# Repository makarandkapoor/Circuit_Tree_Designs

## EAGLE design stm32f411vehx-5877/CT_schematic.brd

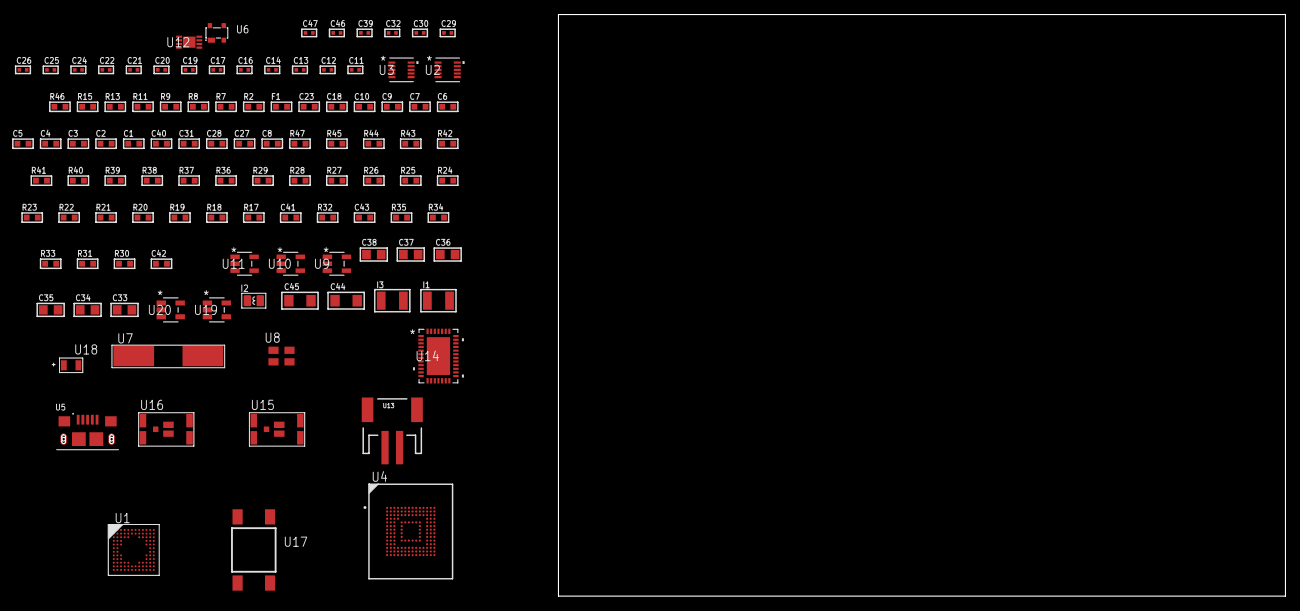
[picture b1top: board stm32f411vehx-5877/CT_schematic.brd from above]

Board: 2 copper layers, 168.3 x 80.0 mm, 108 parts (0 on the bottom side), 65 nets, no tracks yet.

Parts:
C1, C10, C18, C23: 1e-06; C0603
C2, C3, C4, C5, C6, C7: 1e-07; C0603
C8: 4.7e-06; C0603
C9: 1e-08; C0603
C11, C12, C16, C17, C19, C20, C21, C22, C24, C25, C26, C29, C30, C39: 1e-07; C0402
C13, C14: 1e-11; C0402
C27, C28, C31, C40: 2.2e-06; C0603
C32, C46, C47: 1e-08; C0402
C33, C34, C35, C36, C37, C38: 1e-05; C0805
C41: 2.45e-08; R0603
C42: 2.8258362168397e-09; R0603
C43: 7.105e-09; R0603
C44, C45: 1e-05; C1206
F1: 240.0; L0603
I1, I3: 1.5e-05; L1210
I2: 3.3e-06; L0806
R2: 1000.0; R0603
R7, R8: 4700.0; R0603
R9, R11, R13, R15: 2200.0; R0603
R17, R18, R19, R36, R38, R39, R42, R43, R44, R47: 10000.0; R0603
R20, R21, R22, R23, R24, R25, R26, R27, R28, R29: 34000.0; R0603
R30, R31, R33, R34, R35: 1000000.0; R0603
R32: 220000.0; R0603
R37: 75000.0; R0603
R40, R41: 95300.0; R0603
R45: 24000.0; R0603
R46: 2000.0; R0603
U1: STM32F411VEH6; UFBGA100
U2, U3: MAG3110FCR1; DFN-10
U4: mtfc4gmcdm; TFBGA-153
U5: 10118193-0001LF; FCI_10118193-0001LF
U6: prtr5v0u2ax; SOT143B
U7: ABLS-25.000MHZ-B2F-T
U8: ASEK-32.768KHz-ECST; ASEK
U9, U10, U11: ltc3406es5; TSOT-23-5
U12: MCP73831T-2ACI/MC; DFN8_2X3MC
U13: S2B-PH-SM4-TB(LF)(SN); JST-2-SMD
U14: LTC2928CUHF#PBF; QFN-38_UHF
U15, U16: IRF8306MTRPbF; IRF8306MTRPBF
U17: 4-1437565-2; SW_4-1437565-2
U18: Q65110A2395; LGM67K-G1J2-24-Z
U19, U20: nc7sz125m5x; NC7SZ125M5X

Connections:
CLK_CRYSTAL_U1_F1: C13.1, U1.F1, U7.1
CLK_CRYSTAL_U1_G1: C14.1, U1.G1, U7.2
CLK_U1_D1: U1.D1, U8.3
GND: C1.2, C2.2, C3.2, C4.2, C5.2, C6.2, C7.2, C8.2, C9.2, C10.2, C11.2, C12.2, C13.2, C14.2, C16.2, C17.2, C18.2, C19.2, C20.2, C21.2, C22.2, C23.2, C24.2, C25.2, C26.2, C27.2, C28.2, C29.2, C30.2, C31.2, C32.2, C33.2, C34.1, C34.2, C35.2, C36.1, C36.2, C37.2, C38.1, C38.2, C39.2, C40.2, C41.2, C42.2, C43.2, C44.2, C45.2, C46.2, C47.2, R2.2, R17.2, R30.2, R32.2, R34.2, R37.2, R40.2, R41.2, R42.2, R43.2, R44.2, R46.2, U1.D3, U1.F2, U1.F11, U1.F12, U1.J1, U1.K1, U2.5, U2.10, U3.5, U3.10, U4.C4, U4.E7, U4.G5, U4.H10, U4.K8, U4.N2, U4.N5, U4.P4, U4.P6, U5.5, U5.6, U5.7, U5.8, U5.9, U6.1, U8.2, U9.2, U10.2, U11.2, U12.6, U12.9, U13.2, U14.8, U14.9, U14.10, U14.12, U14.13, U14.24, U14.25, U14.30, U14.32, U14.39, U18.C, U19.1, U19.3, U20.1, U20.3
INPUT_USBPOWER_5V: C44.1, R47.2, U5.1, U6.4, U12.1, U12.2
NET_U1_A4: R17.1, U1.A4
NET_U1_A8: R15.1, U1.A8, U2.6
NET_U1_B4: R11.1, U1.B4, U3.6
NET_U1_B5: R9.1, U1.B5, U3.7
NET_U1_C11: C12.1, U1.C11
NET_U1_E3: R19.1, U1.E3
NET_U1_H2: R8.1, U1.H2, U20.4
NET_U1_H3: R18.1, U1.H3
NET_U1_L10: R13.1, U1.L10, U2.7
NET_U1_M1: C9.1, C10.1, F1.1, U1.L1, U1.M1
NET_U1_M12: U17.3, U17.4
NET_U2_1: C16.1, U2.1
NET_U2_4: C19.1, U2.4
NET_U3_1: C21.1, U3.1
NET_U3_4: C24.1, U3.4
NET_U4_C2: C28.1, C29.1, U4.C2
NET_U4_K5: R7.1, U4.K5, U19.4
NET_U9_3: I1.1, U9.3
NET_U9_5: R30.1, R31.1, U9.5
NET_U9_ATNET_3: I1.2, R31.2
NET_U10_3: I2.1, U10.3
NET_U10_5: R32.1, R33.1, U10.5
NET_U10_ATNET_3: I2.2, R33.2
NET_U11_3: I3.1, U11.3
NET_U11_5: R34.1, R35.1, U11.5
NET_U11_ATNET_3: I3.2, R35.2
NET_U12_5: R47.1, U12.5
NET_U12_8: R46.1, U12.8
NET_U14_3: R43.1, U14.3
NET_U14_6: R40.1, U14.6
NET_U14_7: R41.1, U14.7
NET_U14_16: R42.1, R45.1, U14.16
NET_U14_18: R39.1, U14.18
NET_U14_19: R38.1, U14.19, U14.20
NET_U14_21: R36.1, R37.1, U14.21, U19.2, U20.2
NET_U14_26: C42.1, U14.26
NET_U14_27: C41.1, U14.27
NET_U14_28: C43.1, U14.28
NET_U14_38: R44.1, U14.38
NET_U15_3: U14.2, U15.3
NET_U16_3: U14.37, U16.3
NET_U17_1: R2.1, U17.1, U17.2
PROC_SDIO_CK: R29.1, U1.B10, U4.M6
PROC_SDIO_CMD: R28.1, U1.C8, U4.M5
PROC_SDIO_D0: R20.1, U1.A7, U4.A3
PROC_SDIO_D1: R21.1, U1.D11, U4.A4
PROC_SDIO_D2: R22.1, U1.B11, U4.A5
PROC_SDIO_D3: R23.1, U1.C5, U4.B2
PROC_SDIO_D4: R24.1, U1.A3, U4.B3
PROC_SDIO_D5: R25.1, U1.B3, U4.B4
PROC_SDIO_D6: R26.1, U1.E12, U4.B5
PROC_SDIO_D7: R27.1, U1.E11, U4.B6
PROC_USB_OTG_FS_DM: U5.2, U6.3
PROC_USB_OTG_FS_DP: U5.3, U6.2
VCC_3V7: C39.1, C40.1, C45.1, R36.2, R38.2, R39.2, R45.2, U12.3, U12.4, U13.1, U14.11, U14.22, U15.1, U15.2, U15.6, U15.7, U16.1, U16.2, U16.6, U16.7
VCC_S1_3V7: C33.1, C35.1, U9.4, U10.4, U15.4, U15.5
VCC_S2_3V7: C37.1, U11.4, U16.4, U16.5
VCC_TIER1_1V2: C11.1, C34.2, I1.2, R31.2, U1.L11
VCC_TIER1_3V3: C1.1, C2.1, C3.1, C4.1, C5.1, C6.1, C7.1, C8.1, C17.1, C18.1, C20.1, C22.1, C23.1, C25.1, C26.1, C27.1, C30.1, C31.1, C32.1, C36.2, C46.1, C47.1, F1.2, I2.2, R7.2, R8.2, R9.2, R11.2, R13.2, R15.2, R18.2, R19.2, R20.2, R21.2, R22.2, R23.2, R24.2, R25.2, R26.2, R27.2, R28.2, R29.2, R33.2, U1.C4, U1.E2, U1.G2, U1.G11, U1.G12, U2.2, U2.8, U3.2, U3.8, U4.C6, U4.E6, U4.F5, U4.J10, U4.K9, U4.M4, U4.N4, U4.P3, U4.P5, U8.4, U19.5, U20.5
VCC_TIER2_1V2: C38.2, I3.2, R35.2

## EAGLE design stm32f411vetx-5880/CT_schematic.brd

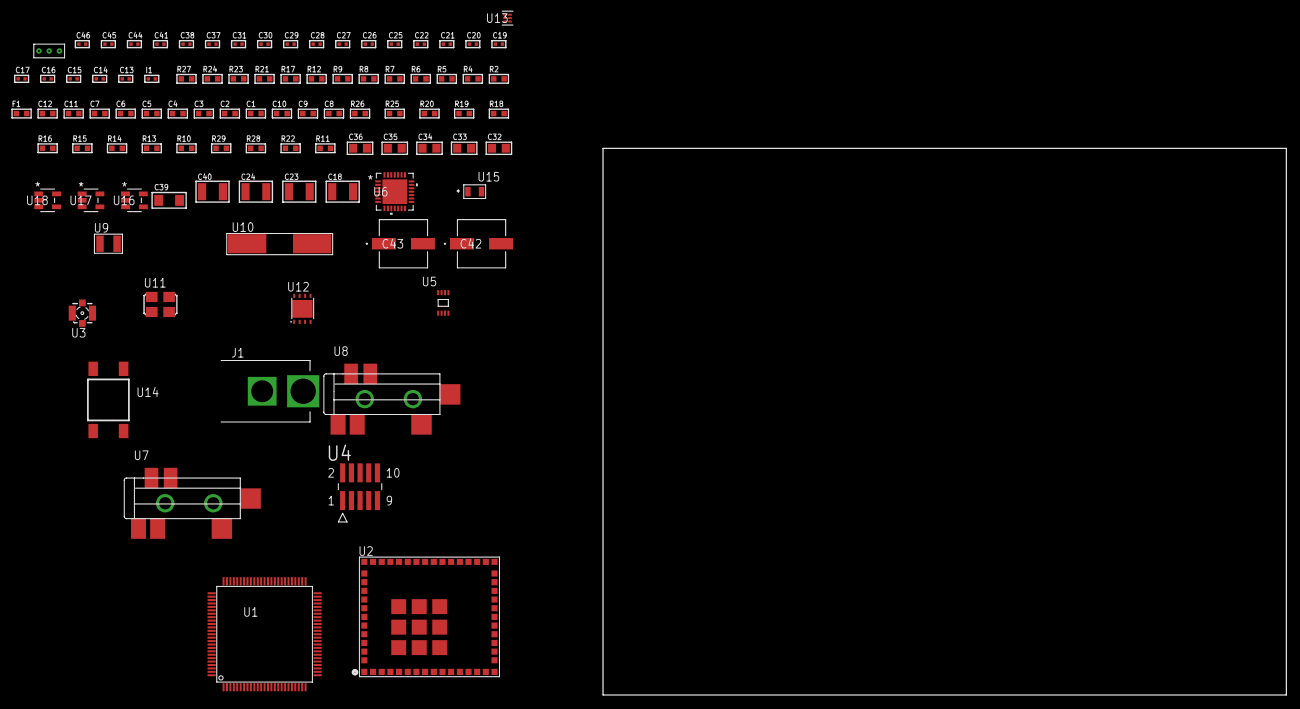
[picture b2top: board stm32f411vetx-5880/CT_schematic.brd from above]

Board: 2 copper layers, 100.0 x 80.0 mm, 95 parts (0 on the bottom side), 44 nets, no tracks yet.

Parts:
C1, C12: 1e-06; C0603
C2, C3, C4, C5, C6, C7: 1e-07; C0603
C8: 4.7e-06; C0603
C9, C10: 2.2e-06; C0603
C11: 1e-08; C0603
C13, C14, C15, C16: 1e-11; C0402
C17: 1e-12; C0402
C18, C23, C24: 2.2e-05; C1210
C19, C20, C21, C27, C28, C29, C30, C31, C41: 1e-07; C0402
C22, C37, C38, C44, C45, C46: 1e-08; C0402
C25, C26: 1e-09; C0402
C32, C33, C34, C35, C36: 1e-05; C0805
C39: 1e-05; C1206
C40: 1e-05; C1210
C42, C43: 0.0001; EXV-9H
F1: 240.0; L0603
I1: 3.6e-09; C0402
J1: PJ-037B; PJ-037B_PACKAGE
R2, R24: 1000.0; R0603
R4, R5: 4700.0; R0603
R6, R7, R8, R9: 2200.0; R0603
R10, R13, R14, R15, R16, R25, R26: 10000.0; R0603
R11, R22: 100000.0; R0603
R12: 2700.0; R0603
R17: 5.0; R0603
R18, R19, R20: 47000.0; R0603
R21: 680.0; R0603
R23: 2231.0; R0603
R27: 9100.0; R0603
R28: 680000.0; R0603
R29: 120000.0; R0603
U1: STM32F411VET6; LQFP100
U2: CC3200MODR1M2AMOBT; LGA63S127P16X13_2050X1750X150
U3: 73412-0114; COAXIAL_C
U4: FTSH-105-01-L-DV-K; SAMTEC_FTSH-105-01-L-DV-K
U5: 24AA01T-I/MNY; TDFN-8/6MM
U6: WM8731CLSEFL; QFN-28
U7, U8: SJ-43515TS-SMT-TR
U9: ABS07-32.768KHZ-7-T
U10: ABLS-25.000MHZ-B2F-T
U11: ASFL1-12.288MHZ-EC-T; ASFL1
U12: LP3878SDX-ADJ/NOPB; WSON-8
U13: TPS3895ADRYR; SON-6
U14: 4-1437565-2; SW_4-1437565-2
U15: Q65110A2395; LGM67K-G1J2-24-Z
U16, U17, U18: nc7sz125m5x; NC7SZ125M5X
U19: Dummy; DUMMY_PACKAGE_205

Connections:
CLK_CRYSTAL_U1_8: C13.1, U1.8, U9.1
CLK_CRYSTAL_U1_9: C14.1, U1.9, U9.2
CLK_CRYSTAL_U1_12: C15.1, U1.12, U10.1
CLK_CRYSTAL_U1_13: C16.1, U1.13, U10.2
CLK_U6_1: U6.1, U11.3
GND: C1.2, C2.2, C3.2, C4.2, C5.2, C6.2, C7.2, C8.2, C9.2, C10.2, C11.2, C12.2, C13.2, C14.2, C15.2, C16.2, C17.2, C18.2, C19.2, C20.2, C21.2, C22.2, C26.2, C27.2, C28.2, C29.2, C30.2, C31.2, C32.2, C33.2, C34.2, C35.2, C36.2, C37.2, C38.2, C39.2, C40.2, C41.2, C42.2, C43.2, C44.2, C45.2, C46.2, J1.2, R2.2, R10.2, R11.2, R12.2, R16.2, R17.2, R18.2, R19.2, R20.2, R24.2, R27.2, R29.2, U1.10, U1.20, U1.27, U1.49, U1.74, U1.99, U2.1, U2.2, U2.16, U2.27, U2.28, U2.30, U2.32, U2.38, U2.43, U2.55, U2.56, U2.57, U2.58, U2.59, U2.60, U2.61, U2.62, U2.63, U3.1, U3.2, U3.3, U3.4, U4.3, U4.5, U5.4, U5.7, U6.4, U6.15, U6.19, U6.25, U6.26, U6.29, U7.1, U8.1, U11.2, U12.3, U12.PAD, U13.2, U15.C, U16.2, U16.3, U17.1, U17.3, U18.1, U18.3, U19.1
NET_U1_14: R5.1, U1.14, U18.4
NET_U1_22: C11.1, C12.1, F1.1, U1.21, U1.22
NET_U1_47: R8.1, U1.47, U5.6
NET_U1_48: C9.1, U1.48
NET_U1_73: C10.1, U1.73
NET_U1_92: R6.1, U1.92, U2.3
NET_U1_93: R7.1, U1.93, U2.4
NET_U1_94: R10.1, U1.94
NET_U1_96: R9.1, U1.96, U5.5
NET_U1_98: U14.3, U14.4
NET_U2_21: R11.1, U2.21
NET_U2_23: R12.1, U2.23
NET_U2_35: R4.1, U2.35, U17.4
NET_U3_1: C17.1, I1.1, U3.1
NET_U4_9: R17.1, U4.9
NET_U6_20: C31.1, C36.1, U6.20
NET_U7_2: C24.1, R19.1, U7.2
NET_U7_5: C23.1, R18.1, U7.5
NET_U8_5: C25.1, C26.1, R20.1, R21.1, U8.5
NET_U12_1: C38.1, U12.1
NET_U12_6: R23.2, R24.1, U12.6
NET_U12_8: R22.1, U12.8
NET_U13_1: R26.1, R27.1, U13.1
NET_U13_3: R28.2, R29.1, U13.3
NET_U13_4: R25.1, U13.4, U16.4, U17.2, U18.2
NET_U14_1: R2.1, U14.1, U14.2
PROC_ADC1_IN1: U1.24, U19.3
PROC_ADC1_IN2: U1.25, U19.2
PROC_I2S1_CK: U1.30, U6.7
PROC_I2S1_SD: U1.32, U6.8
PROC_I2S1_WS: U1.29, U6.9, U6.11
PROC_SYS_JTCK_SWCLK: R16.1, U1.76, U4.4
PROC_SYS_JTDI: R14.1, U1.77, U4.8
PROC_SYS_JTDO_SWO: U1.89, U4.6
PROC_SYS_JTMS_SWDIO: R15.1, U1.72, U4.2
RST_OUT_U4_JTAG_RST_B: R13.1, U4.10, U16.1
VCC_S1_5V4: C39.1, C42.1, C43.1, J1.1, R22.2, U12.4
VCC_TIER1_3V3: C1.1, C2.1, C3.1, C4.1, C5.1, C6.1, C7.1, C8.1, C18.1, C19.1, C20.1, C21.1, C22.1, C27.1, C28.1, C29.1, C30.1, C32.1, C33.1, C34.1, C35.1, C37.1, C40.1, C41.1, C44.1, C45.1, C46.1, F1.2, R4.2, R5.2, R6.2, R7.2, R8.2, R9.2, R13.2, R14.2, R15.2, R23.1, R25.2, R26.2, R28.1, U1.6, U1.11, U1.19, U1.28, U1.50, U1.75, U1.100, U2.36, U2.37, U2.40, U4.1, U5.8, U6.3, U6.5, U6.12, U6.18, U11.4, U12.5, U13.6, U16.5, U17.5, U18.5

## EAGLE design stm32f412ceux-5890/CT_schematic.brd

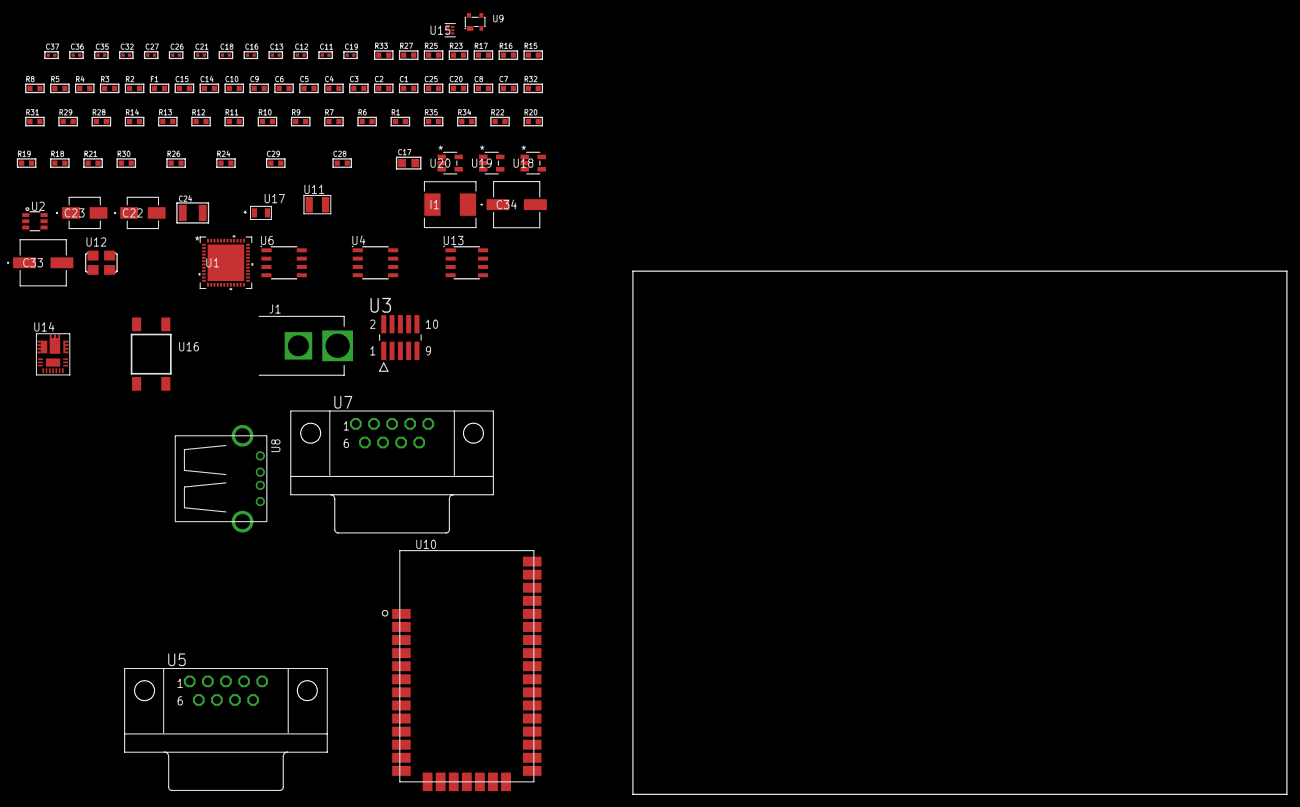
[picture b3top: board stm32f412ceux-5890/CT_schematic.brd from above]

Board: 2 copper layers, 100.0 x 80.0 mm, 93 parts (0 on the bottom side), 59 nets, no tracks yet.

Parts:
C1, C10, C14, C15: 1e-06; C0603
C2, C3, C4, C5, C6: 1e-07; C0603
C7: 4.7e-06; C0603
C8, C25: 2.2e-06; C0603
C9: 1e-08; C0603
C11, C12: 1e-11; C0402
C13, C16, C18, C26, C27, C32: 1e-07; C0402
C17: 1e-05; C0805
C19: 4.7e-11; C0402
C20: 8.2e-12; C0603
C21, C35, C36, C37: 1e-08; C0402
C22: 1e-06; EXV-9B
C23: 2.2e-06; EXV-9B
C24: 0.0001; C1210
C28: 8.6971073877236e-09; R0603
C29: 2.9649229730876e-07; R0603
C33, C34: 0.0001; EXV-9H
F1: 240.0; L0603
I1: 6.8e-07; IND25X25CZ
J1: PJ-037B; PJ-037B_PACKAGE
R1, R7, R9, R10, R11, R12, R13, R14, R31, R32: 10000.0; R0603
R2: 1000.0; R0603
R3: 1600.5; R0603
R4, R5: 4700.0; R0603
R6: 47000.0; R0603
R8: 1270.0; R0603
R15: 5.0; R0603
R16, R17: 120.0; R0603
R18: 470000.0; R0603
R19, R20, R22: 100000.0; R0603
R21: 164658.62; R0603
R23: 0.1; R0603
R24: 4030.2416170974; R0603
R25: 453.0; R0603
R26: 58.613333333333; R0603
R27: 130.0; R0603
R28: 39000.0; R0603
R29: 49900.0; R0603
R30: 5147.5789473684; R0603
R33: 9100.0; R0603
R34: 680000.0; R0603
R35: 120000.0; R0603
U1: STM32F412CEU6; UFQFPN48
U2: MAX4995AAUT+T; SOT-23-6
U3: FTSH-105-01-L-DV-K; SAMTEC_FTSH-105-01-L-DV-K
U4: MCP2562-E/SN; SOIC-8
U5, U7: 182-009-113R531; 182-009-MALE
U6: SN65HVD230D; SOIC-8
U8: 61400416021; USB-A-H
U9: prtr5v0u2ax; SOT143B
U10: XB24CZ7UIS-004
U11: ABS07-32.768KHZ-7-T
U12: ASFL1-25MHZ-NCS; ASFL1
U13: LP2954AIMX/NOPB; LP2954
U14: IR3899MTR1PBF
U15: TPS3895ADRYR; SON-6
U16: 4-1437565-2; SW_4-1437565-2
U17: Q65110A2395; LGM67K-G1J2-24-Z
U18, U19, U20: nc7sz125m5x; NC7SZ125M5X

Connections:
CLK_CRYSTAL_U1_3: C11.1, U1.3, U11.1
CLK_CRYSTAL_U1_4: C12.1, U1.4, U11.2
CLK_U1_5: U1.5, U12.3
GND: C1.2, C2.2, C3.2, C4.2, C5.2, C6.2, C7.2, C8.2, C9.2, C10.2, C11.2, C12.2, C13.2, C14.2, C15.2, C16.2, C17.2, C18.2, C19.2, C20.2, C21.2, C22.2, C23.2, C25.2, C26.2, C27.2, C32.2, C33.2, C34.2, C35.2, C36.2, C37.2, J1.2, R2.2, R6.2, R7.2, R8.2, R10.2, R14.2, R15.2, R18.2, R22.2, R23.1, R23.2, R25.2, R28.2, R30.2, R33.2, R35.2, U1.8, U1.23, U1.35, U1.47, U1.49, U2.2, U3.3, U3.5, U4.2, U4.8, U5.5, U6.2, U7.5, U8.4, U8.5, U8.6, U9.1, U10.1, U10.11, U10.13, U10.22, U10.35, U12.2, U13.4, U14.4, U14.11, U14.17, U15.2, U17.C, U18.2, U18.3, U19.1, U19.3, U20.1, U20.3
NET_U1_7: R5.1, U1.7, U20.4
NET_U1_9: C9.1, C10.1, F1.1, U1.9
NET_U1_22: C8.1, U1.22
NET_U1_31: R8.1, U1.31
NET_U1_42: R3.1, U1.42, U17.A
NET_U1_43: R1.1, U1.43, U16.3, U16.4
NET_U1_44: R7.1, U1.44
NET_U2_3: R6.1, U2.3
NET_U3_9: R15.1, U3.9
NET_U4_6: R16.2, U4.6
NET_U5_2: R16.2, U4.6, U5.2
NET_U5_3: R16.1, U4.7, U5.3
NET_U6_6: R17.2, U6.6
NET_U6_8: R18.1, U6.8
NET_U7_2: R17.2, U6.6, U7.2
NET_U7_3: R17.1, U6.7, U7.3
NET_U10_6: R4.1, U10.6, U19.4
NET_U13_3: R20.1, U13.3
NET_U13_5: R19.1, U13.5
NET_U13_7: R21.2, R22.1, U13.7
NET_U14_1: C28.1, R24.1, R25.1, R26.1, R27.1, U14.1, U14.8
NET_U14_2: C27.1, U14.2
NET_U14_3: C28.2, C29.1, C29.2, U14.3
NET_U14_5: R28.1, U14.5
NET_U14_10: C25.1, U14.10
NET_U14_12: C24.1, I1.1, U14.12
NET_U14_14: C24.2, U14.14
NET_U14_15: R29.1, R30.1, U14.15
NET_U14_ATNET_3: I1.2, R24.2
NET_U14_ATNET_4: C29.2, R26.2
NET_U15_1: R32.1, R33.1, U15.1
NET_U15_3: R34.2, R35.1, U15.3
NET_U15_4: R31.1, U15.4, U18.4, U19.2, U20.2
NET_U16_1: R2.1, U16.1, U16.2
PROC_CAN1_RX: U1.45, U6.4
PROC_CAN1_TX: U1.46, U6.1
PROC_CAN2_RX: U1.25, U4.4
PROC_CAN2_TX: U1.26, U4.1
PROC_GPIO_TO_U1_USB_FAULT: R9.1, U1.6, U2.6
PROC_GPIO_TO_U1_VBUS_EN: R10.1, U1.2, U2.4
PROC_SPI1_MISO: U1.16, U10.17
PROC_SPI1_MOSI: U1.17, U10.16
PROC_SPI1_NSS: U1.14, U10.15
PROC_SPI1_SCK: U1.15, U10.14
PROC_SYS_JTCK_SWCLK: R14.1, U1.37, U3.4
PROC_SYS_JTDI: R12.1, U1.38, U3.8
PROC_SYS_JTDO_SWO: U1.39, U3.6
PROC_SYS_JTMS_SWDIO: R13.1, U1.34, U3.2
PROC_USB_OTG_FS_DM: U1.32, U8.2, U9.3
PROC_USB_OTG_FS_DP: U1.33, U8.3, U9.2
PROC_USB_OTG_FS_VBUS: U1.30, U2.1, U8.1, U9.4
RST_OUT_U3_JTAG_RST_B: R11.1, U3.10, U18.1
VCC_S1_16V8: C22.1, C26.1, C33.1, C34.1, J1.1, R20.2, R29.2, U13.8, U14.9
VCC_TIER1_3V3: C1.1, C2.1, C3.1, C4.1, C5.1, C6.1, C7.1, C13.1, C15.1, C16.1, C17.1, C18.1, C19.1, C20.1, C21.1, C23.1, C32.1, C35.1, C36.1, C37.1, F1.2, R1.2, R3.2, R4.2, R5.2, R9.2, R11.2, R12.2, R13.2, R19.2, R21.1, R31.2, R32.2, R34.1, U1.1, U1.24, U1.36, U1.48, U3.1, U4.5, U6.3, U10.2, U10.27, U12.4, U13.1, U15.6, U18.5, U19.5, U20.5
VCC_TIER1_5V0: C14.1, I1.2, R24.2, U2.5, U4.3

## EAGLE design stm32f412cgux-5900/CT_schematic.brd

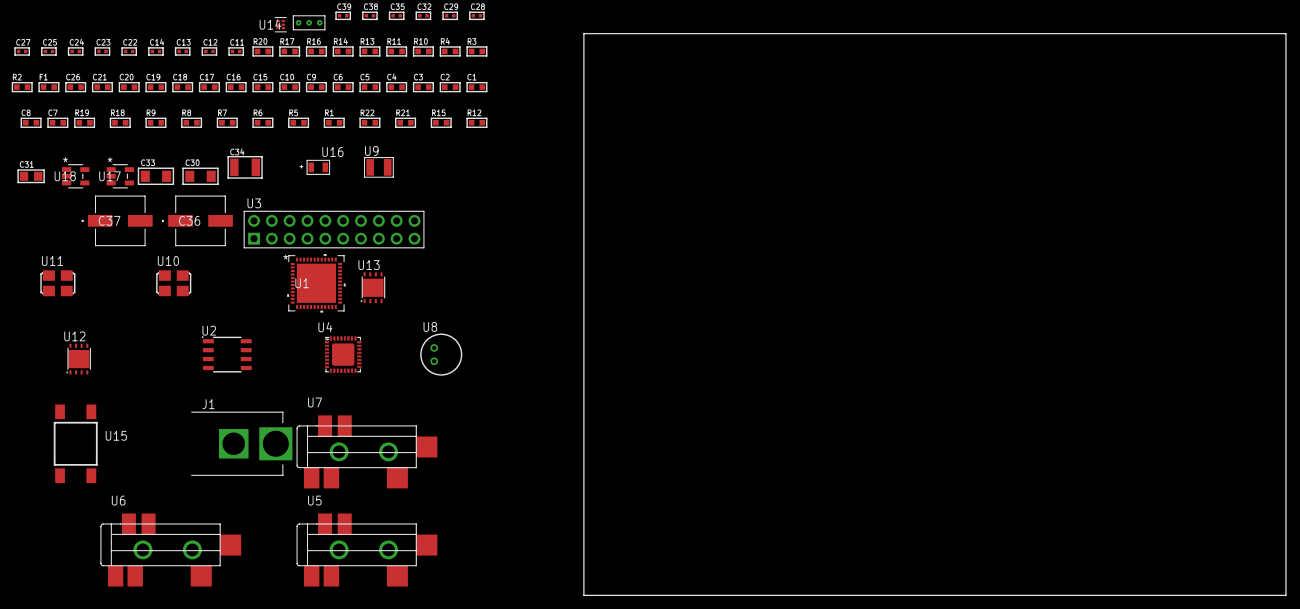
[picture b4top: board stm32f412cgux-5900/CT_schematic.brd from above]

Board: 2 copper layers, 100.0 x 80.0 mm, 82 parts (0 on the bottom side), 52 nets, no tracks yet.

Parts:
C1, C10, C15, C16, C17, C18, C19, C20, C21, C26: 1e-06; C0603
C2, C3, C4, C5, C6: 1e-07; C0603
C7: 4.7e-06; C0603
C8: 2.2e-06; C0603
C9: 1e-08; C0603
C11, C12: 1e-11; C0402
C13, C27, C28, C29, C32, C38, C39: 1e-08; C0402
C14, C22, C23, C24, C25, C35: 1e-07; C0402
C30, C33: 1e-05; C1206
C31: 1e-05; C0805
C34: 1e-05; C1210
C36, C37: 0.0001; EXV-9H
F1: 240.0; L0603
J1: PJ-037B; PJ-037B_PACKAGE
R1, R5, R6, R7, R8, R9, R18, R19: 10000.0; R0603
R2, R14, R17: 1000.0; R0603
R3: 1600.5; R0603
R4: 4700.0; R0603
R10, R11: 1270.0; R0603
R12, R15: 100000.0; R0603
R13: 200.0; R0603
R16: 2231.0; R0603
R20: 9100.0; R0603
R21: 680000.0; R0603
R22: 120000.0; R0603
U1: STM32F412CGU6; UFQFPN48
U2: AT25640B-SSHL-T; SOIC-8
U3: TST-110-05-T-D-RA
U4: SGTL5000XNAA3; QFN-32
U5, U6, U7: SJ-43515TS-SMT-TR
U8: WM-64PCT; WM-64PC
U9: ABS07-32.768KHZ-7-T
U10: ASFL-24.57MHZ-NCS; ASFL1
U11: ASFL1-25MHZ-NCS; ASFL1
U12, U13: LP3878SDX-ADJ/NOPB; WSON-8
U14: TPS3895ADRYR; SON-6
U15: 4-1437565-2; SW_4-1437565-2
U16: Q65110A2395; LGM67K-G1J2-24-Z
U17, U18: nc7sz125m5x; NC7SZ125M5X
U19: Dummy; DUMMY_PACKAGE_166

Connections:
CLK_CRYSTAL_U1_3: C11.1, U1.3, U9.1
CLK_CRYSTAL_U1_4: C12.1, U1.4, U9.2
CLK_U1_5: U1.5, U11.3
CLK_U4_21: U4.21, U10.3
GND: C1.2, C2.2, C3.2, C4.2, C5.2, C6.2, C7.2, C8.2, C9.2, C10.2, C11.2, C12.2, C13.2, C14.2, C22.2, C23.2, C24.2, C25.2, C26.2, C27.2, C28.2, C29.2, C30.2, C31.2, C32.2, C33.2, C34.2, C35.2, C36.2, C37.2, C38.2, C39.2, J1.2, R2.2, R5.2, R11.2, R14.2, R17.2, R20.2, R22.2, U1.8, U1.23, U1.35, U1.47, U1.49, U2.4, U3.4, U3.6, U3.8, U3.10, U3.12, U3.14, U3.16, U3.18, U3.20, U4.1, U4.3, U4.7, U4.EXP, U6.1, U7.1, U8.2, U10.2, U11.2, U12.3, U12.PAD, U13.3, U13.PAD, U14.2, U16.C, U17.2, U17.3, U18.1, U18.3, U19.1
NET_U1_7: R4.1, U1.7, U18.4
NET_U1_9: C9.1, C10.1, F1.1, U1.9
NET_U1_22: C8.1, U1.22
NET_U1_44: R5.1, U1.44
NET_U1_45: R3.1, U1.45, U16.A
NET_U1_46: R1.1, U1.46, U15.3, U15.4
NET_U2_3: R6.1, U2.3
NET_U2_7: R8.1, U2.7
NET_U4_10: C25.1, U4.10
NET_U4_29: R10.1, U4.29
NET_U4_31: R11.1, U4.31
NET_U5_1: U4.4, U5.1
NET_U5_2: U4.2, U5.2
NET_U5_5: U4.6, U5.5
NET_U6_2: C16.1, U6.2
NET_U6_5: C15.1, U6.5
NET_U7_2: C18.1, C19.1, U7.2
NET_U7_5: C17.1, U7.5
NET_U7_13: C18.2, C19.2
NET_U8_1: C20.1, C21.1, C26.1, U4.16, U8.1
NET_U8_15: C20.2, C21.2
NET_U12_1: C29.1, U12.1
NET_U12_6: R13.2, R14.1, U12.6
NET_U12_8: R12.1, U12.8
NET_U13_1: C32.1, U13.1
NET_U13_6: R16.2, R17.1, U13.6
NET_U13_8: R15.1, U13.8
NET_U14_1: R19.1, R20.1, U14.1
NET_U14_3: R21.2, R22.1, U14.3
NET_U14_4: R18.1, U14.4, U17.4, U18.2
NET_U15_1: R2.1, U15.1, U15.2
PROC_I2S1_CK: U1.15, U4.24
PROC_I2S1_SD: U1.17, U4.26
PROC_I2S1_WS: U1.14, U4.23
PROC_SPI2_MISO: U1.27, U2.2
PROC_SPI2_MOSI: U1.28, U2.5
PROC_SPI2_NSS: R7.1, U1.25, U2.1
PROC_SPI2_SCK: U1.21, U2.6
PROC_SYS_JTCK_SWCLK: U1.37, U3.9
PROC_SYS_JTDO_SWO: U1.39, U3.13
PROC_SYS_JTMS_SWDIO: U1.34, U3.7
PROC_TIM1_CH2: U1.30, U19.2
PROC_TIM1_CH4: U1.32, U19.3
RST_OUT_U3_SRESET_B: R9.1, U3.15, U17.1
VCC_S1_9V6: C30.1, C33.1, C36.1, C37.1, J1.1, R12.2, R15.2, U12.4, U13.4
VCC_TIER1_1V2: C22.1, C31.1, R13.1, U4.30, U12.5
VCC_TIER1_3V3: C1.1, C2.1, C3.1, C4.1, C5.1, C6.1, C7.1, C13.1, C14.1, C23.1, C24.1, C27.1, C28.1, C34.1, C35.1, C38.1, C39.1, F1.2, R1.2, R3.2, R4.2, R6.2, R7.2, R8.2, R9.2, R10.2, R16.1, R18.2, R19.2, R21.1, U1.1, U1.24, U1.36, U1.48, U2.8, U3.1, U4.5, U4.20, U10.4, U11.4, U13.5, U14.6, U17.5, U18.5

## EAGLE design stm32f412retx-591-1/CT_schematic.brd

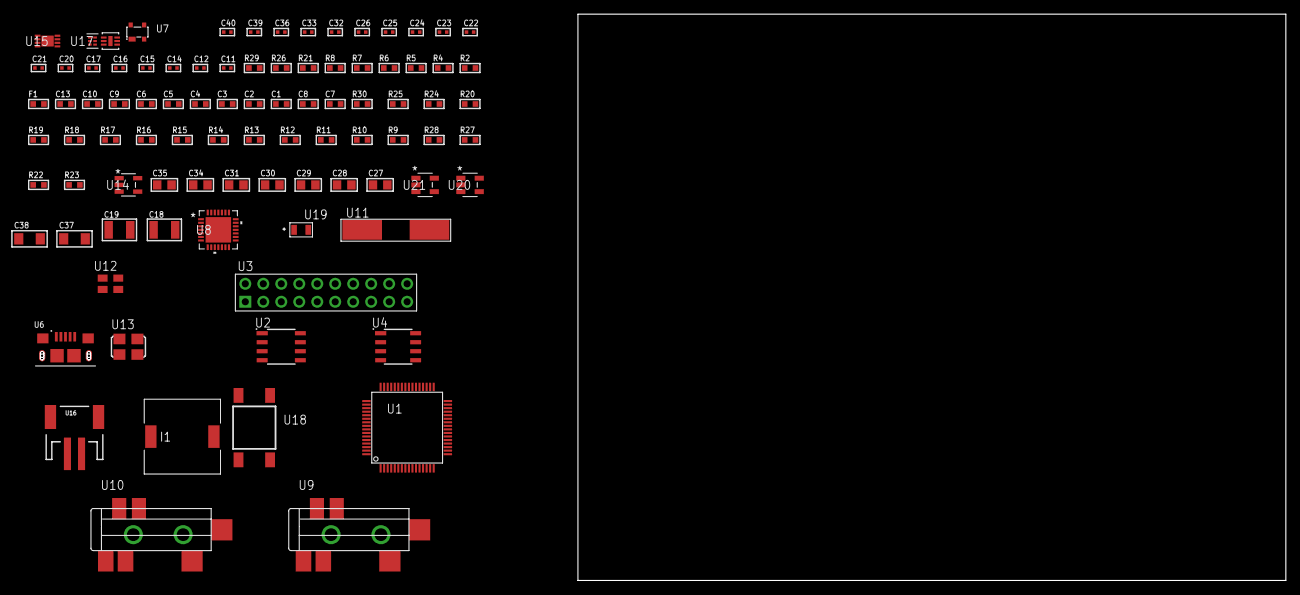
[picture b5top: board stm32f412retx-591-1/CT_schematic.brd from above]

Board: 2 copper layers, 175.9 x 80.0 mm, 91 parts (0 on the bottom side), 50 nets, no tracks yet.

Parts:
C1, C10, C13: 1e-06; C0603
C2, C3, C4, C5, C6: 1e-07; C0603
C7: 4.7e-06; C0603
C8: 2.2e-06; C0603
C9: 1e-08; C0603
C11, C12: 1e-11; C0402
C14, C16, C32, C33, C39, C40: 1e-08; C0402
C15, C17, C22, C23, C24, C25, C26, C36: 1e-07; C0402
C18, C19: 2.2e-05; C1210
C20, C21: 1e-09; C0402
C27, C28, C29, C30, C31, C34, C35: 1e-05; C0805
C37, C38: 1e-05; C1206
F1: 240.0; L0603
I1: 5.2e-06; DR1040
R2: 1000.0; R0603
R4: 4700.0; R0603
R5, R6, R7, R8: 2200.0; R0603
R9, R10, R11, R12, R13, R14, R15, R16, R17, R24, R25, R30: 10000.0; R0603
R18, R19, R20: 47000.0; R0603
R21: 680.0; R0603
R22: 220000.0; R0603
R23: 1000000.0; R0603
R26: 9100.0; R0603
R27: 680000.0; R0603
R28: 120000.0; R0603
R29: 2000.0; R0603
U1: STM32F412RET6; LQFP64
U2: AT25M01-SSHM-T; SOIC-8
U3: TST-110-05-T-D-RA
U4: AT24C02D-SSHM-T; AT24C02D
U5: SI7006-A20-IM; DFN-6
U6: 10118193-0001LF; FCI_10118193-0001LF
U7: prtr5v0u2ax; SOT143B
U8: WM8731CLSEFL; QFN-28
U9, U10: SJ-43515TS-SMT-TR
U11: ABLS-25.000MHZ-B2F-T
U12: ASEK-32.768KHz-ECST; ASEK
U13: ASFL1-12.288MHZ-EC-T; ASFL1
U14: ltc3406es5; TSOT-23-5
U15: MCP73831T-2ACI/MC; DFN8_2X3MC
U16: S2B-PH-SM4-TB(LF)(SN); JST-2-SMD
U17: TPS3895ADRYR; SON-6
U18: 4-1437565-2; SW_4-1437565-2
U19: Q65110A2395; LGM67K-G1J2-24-Z
U20, U21: nc7sz125m5x; NC7SZ125M5X

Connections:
CLK_CRYSTAL_U1_5: C11.1, U1.5, U11.1
CLK_CRYSTAL_U1_6: C12.1, U1.6, U11.2
CLK_U1_3: U1.3, U12.3
CLK_U8_1: U8.1, U13.3
GND: C1.2, C2.2, C3.2, C4.2, C5.2, C6.2, C7.2, C8.2, C9.2, C10.2, C11.2, C12.2, C13.2, C14.2, C15.2, C16.2, C17.2, C21.2, C22.2, C23.2, C24.2, C25.2, C26.2, C27.2, C28.2, C29.2, C30.2, C31.2, C32.2, C33.2, C34.2, C35.1, C35.2, C36.2, C37.2, C38.2, C39.2, C40.2, R2.2, R9.2, R14.2, R16.2, R17.2, R18.2, R19.2, R20.2, R22.2, R26.2, R28.2, R29.2, U1.12, U1.18, U1.31, U1.44, U1.47, U1.63, U2.4, U3.4, U3.6, U3.8, U3.10, U3.12, U3.14, U3.16, U3.18, U3.20, U4.4, U5.2, U5.7, U6.5, U6.6, U6.7, U6.8, U6.9, U7.1, U8.4, U8.15, U8.19, U8.25, U8.26, U8.29, U9.1, U10.1, U12.2, U13.2, U14.2, U15.6, U15.9, U16.2, U17.2, U19.C, U20.2, U20.3, U21.1, U21.3
INPUT_USBPOWER_5V: C13.1, C37.1, R30.2, U1.42, U6.1, U7.4, U15.1, U15.2
NET_U1_7: R4.1, U1.7, U21.4
NET_U1_13: C9.1, C10.1, F1.1, U1.13
NET_U1_29: R7.1, U1.29, U4.6
NET_U1_30: C8.1, U1.30
NET_U1_58: R5.1, U1.58, U5.6
NET_U1_59: R6.1, U1.59, U5.1
NET_U1_60: R9.1, U1.60
NET_U1_61: U18.3, U18.4
NET_U1_62: R8.1, U1.62, U4.5
NET_U2_3: R10.1, U2.3
NET_U2_7: R12.1, U2.7
NET_U4_1: R15.1, U4.1
NET_U4_2: R16.1, U4.2
NET_U4_3: R17.1, U4.3
NET_U4_7: R14.1, U4.7
NET_U8_20: C26.1, C31.1, U8.20
NET_U9_2: C19.1, R19.1, U9.2
NET_U9_5: C18.1, R18.1, U9.5
NET_U10_5: C20.1, C21.1, R20.1, R21.1, U10.5
NET_U14_3: I1.1, U14.3
NET_U14_5: R22.1, R23.1, U14.5
NET_U14_ATNET_3: I1.2, R23.2
NET_U15_5: R30.1, U15.5
NET_U15_8: R29.1, U15.8
NET_U17_1: R25.1, R26.1, U17.1
NET_U17_3: R27.2, R28.1, U17.3
NET_U17_4: R24.1, U17.4, U20.4, U21.2
NET_U18_1: R2.1, U18.1, U18.2
PROC_I2S2_CK: U1.34, U8.7
PROC_I2S2_EXT_SD: U1.10, U8.10
PROC_I2S2_SD: U1.11, U8.8
PROC_I2S2_WS: U1.33, U8.9, U8.11
PROC_SPI1_MISO: U1.22, U2.2
PROC_SPI1_MOSI: U1.23, U2.5
PROC_SPI1_NSS: R11.1, U1.20, U2.1
PROC_SPI1_SCK: U1.21, U2.6
PROC_SYS_JTCK_SWCLK: U1.49, U3.9
PROC_SYS_JTDO_SWO: U1.55, U3.13
PROC_SYS_JTMS_SWDIO: U1.46, U3.7
PROC_USB_OTG_FS_DM: U1.44, U6.2, U7.3
PROC_USB_OTG_FS_DP: U1.45, U6.3, U7.2
RST_OUT_U3_SRESET_B: R13.1, U3.15, U20.1
VCC_S1_3V7: C34.1, C38.1, U14.4, U15.3, U15.4, U16.1
VCC_TIER1_3V3: C1.1, C2.1, C3.1, C4.1, C5.1, C6.1, C7.1, C14.1, C15.1, C16.1, C17.1, C22.1, C23.1, C24.1, C25.1, C27.1, C28.1, C29.1, C30.1, C32.1, C33.1, C35.2, C36.1, C39.1, C40.1, F1.2, I1.2, R4.2, R5.2, R6.2, R7.2, R8.2, R10.2, R11.2, R12.2, R13.2, R15.2, R23.2, R24.2, R25.2, R27.1, U1.1, U1.19, U1.32, U1.48, U1.64, U2.8, U3.1, U4.8, U5.5, U8.3, U8.5, U8.12, U8.18, U12.4, U13.4, U17.6, U20.5, U21.5

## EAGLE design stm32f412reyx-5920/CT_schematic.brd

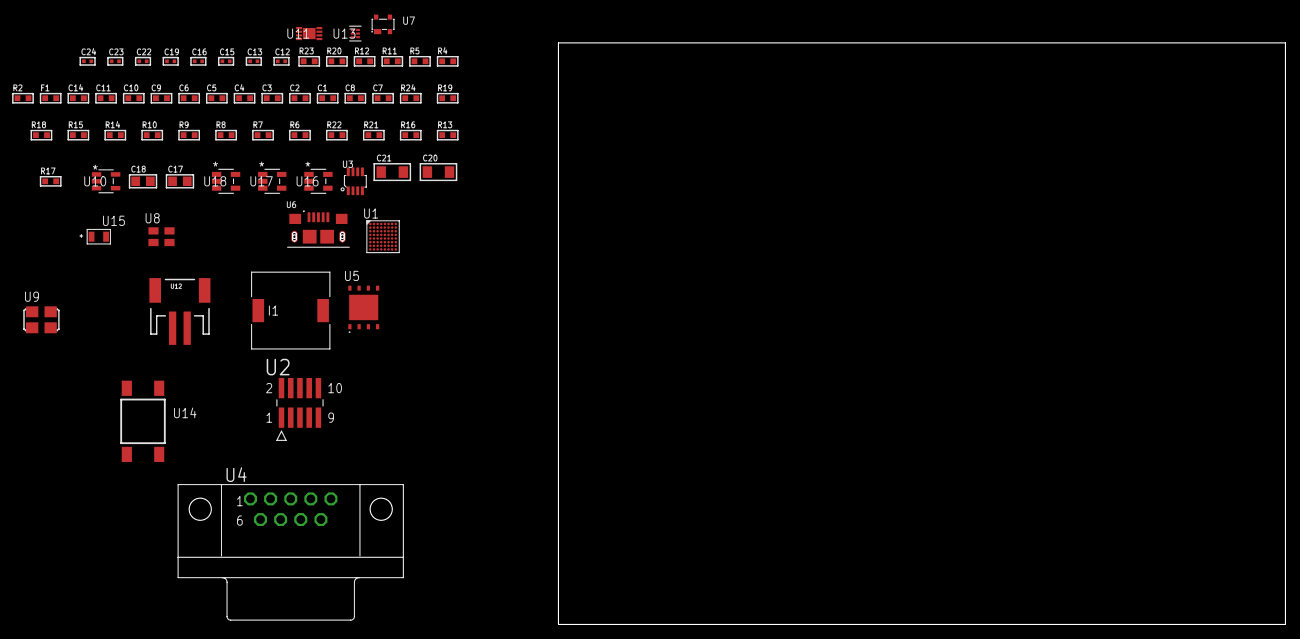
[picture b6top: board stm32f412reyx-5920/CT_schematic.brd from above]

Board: 2 copper layers, 66 parts (0 on the bottom side), 40 nets, no tracks yet.

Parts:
C1, C10, C11, C14: 1e-06; C0603
C2, C3, C4, C5, C6: 1e-07; C0603
C7: 4.7e-06; C0603
C8: 2.2e-06; C0603
C9: 1e-08; C0603
C12, C13, C19: 1e-07; C0402
C15, C16, C22, C23, C24: 1e-08; C0402
C17, C18: 1e-05; C0805
C20, C21: 1e-05; C1206
F1: 240.0; L0603
I1: 3.8e-06; DR1040
R2: 1000.0; R0603
R4, R5: 4700.0; R0603
R6, R7, R8, R9, R10, R14, R15, R18, R19, R24: 10000.0; R0603
R11: 5.0; R0603
R12: 120.0; R0603
R13: 100000.0; R0603
R16: 220000.0; R0603
R17: 1000000.0; R0603
R20: 9100.0; R0603
R21: 680000.0; R0603
R22: 120000.0; R0603
R23: 2000.0; R0603
U1: STM32F412REY6; WLCSP64
U2: FTSH-105-01-L-DV-K; SAMTEC_FTSH-105-01-L-DV-K
U3: MAX3051EKA+T; SOT-23-8
U4: 182-009-113R531; 182-009-MALE
U5: MX25R6435FZAIH0; WSON-8-PAD
U6: 10118193-0001LF; FCI_10118193-0001LF
U7: prtr5v0u2ax; SOT143B
U8: ASEK-32.768KHz-ECST; ASEK
U9: ASFL1-25MHZ-NCS; ASFL1
U10: ltc3406es5; TSOT-23-5
U11: MCP73831T-2ACI/MC; DFN8_2X3MC
U12: S2B-PH-SM4-TB(LF)(SN); JST-2-SMD
U13: TPS3895ADRYR; SON-6
U14: 4-1437565-2; SW_4-1437565-2
U15: Q65110A2395; LGM67K-G1J2-24-Z
U16, U17, U18: nc7sz125m5x; NC7SZ125M5X

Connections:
CLK_U1_C8: U1.C8, U8.3
CLK_U1_D8: U1.D8, U9.3
GND: C1.2, C2.2, C3.2, C4.2, C5.2, C6.2, C7.2, C8.2, C9.2, C10.2, C11.2, C12.2, C13.2, C14.2, C15.2, C16.2, C17.2, C18.1, C18.2, C19.2, C20.2, C21.2, C22.2, C23.2, C24.2, R2.2, R6.2, R7.2, R11.2, R13.2, R16.2, R20.2, R22.2, R23.2, U1.A7, U1.B1, U1.D3, U1.G8, U1.H2, U2.3, U2.5, U3.2, U4.5, U5.4, U5.PAD, U6.5, U6.6, U6.7, U6.8, U6.9, U7.1, U8.2, U9.2, U10.2, U11.6, U11.9, U12.2, U13.2, U15.C, U16.2, U16.3, U17.1, U17.3, U18.1, U18.3
INPUT_USBPOWER_5V: C11.1, C20.1, R24.2, U1.D1, U6.1, U7.4, U11.1, U11.2
NET_U1_C6: R7.1, U1.C6
NET_U1_D4: R6.1, U1.D4
NET_U1_D7: R5.1, U1.D7, U18.4
NET_U1_F7: C9.1, C10.1, F1.1, U1.F7
NET_U1_H3: C8.1, U1.H3
NET_U1_H8: U14.3, U14.4
NET_U2_9: R11.1, U2.9
NET_U3_6: R12.2, U3.6
NET_U3_8: R13.1, U3.8
NET_U4_2: R12.2, U3.6, U4.2
NET_U4_3: R12.1, U3.7, U4.3
NET_U5_7: R4.1, U1.G7, U5.7, U17.4
NET_U10_3: I1.1, U10.3
NET_U10_5: R16.1, R17.1, U10.5
NET_U10_ATNET_3: I1.2, R17.2
NET_U11_5: R24.1, U11.5
NET_U11_8: R23.1, U11.8
NET_U13_1: R19.1, R20.1, U13.1
NET_U13_3: R21.2, R22.1, U13.3
NET_U13_4: R18.1, U13.4, U16.4, U17.2, U18.2
NET_U14_1: R2.1, U14.1, U14.2
PROC_CAN1_RX: U1.C5, U3.4
PROC_CAN1_TX: U1.B6, U3.1
PROC_QUADSPI_BK1_IO0: U1.E2, U5.5
PROC_QUADSPI_BK1_IO1: U1.C3, U5.2
PROC_QUADSPI_BK1_IO2: R15.1, U1.F3, U5.3
PROC_QUADSPI_BK1_NCS: R14.1, U1.B5, U5.1
PROC_QUADSPI_CLK: U1.F4, U5.6
PROC_SYS_JTCK_SWCLK: R9.1, U1.B2, U2.4
PROC_SYS_JTDO_SWO: U1.A5, U2.6
PROC_SYS_JTMS_SWDIO: R10.1, U1.C2, U2.2
PROC_USB_OTG_FS_DM: U1.D3, U6.2, U7.3
PROC_USB_OTG_FS_DP: U1.C1, U6.3, U7.2
RST_OUT_U2_JTAG_RST_B: R8.1, U2.10, U16.1
VCC_S1_3V7: C17.1, C21.1, U10.4, U11.3, U11.4, U12.1
VCC_TIER1_3V3: C1.1, C2.1, C3.1, C4.1, C5.1, C6.1, C7.1, C12.1, C13.1, C14.1, C15.1, C16.1, C18.2, C19.1, C22.1, C23.1, C24.1, F1.2, I1.2, R4.2, R5.2, R8.2, R9.2, R10.2, R14.2, R15.2, R17.2, R18.2, R19.2, R21.1, U1.A1, U1.A8, U1.B7, U1.H1, U1.H7, U2.1, U3.3, U5.8, U8.4, U9.4, U13.6, U16.5, U17.5, U18.5

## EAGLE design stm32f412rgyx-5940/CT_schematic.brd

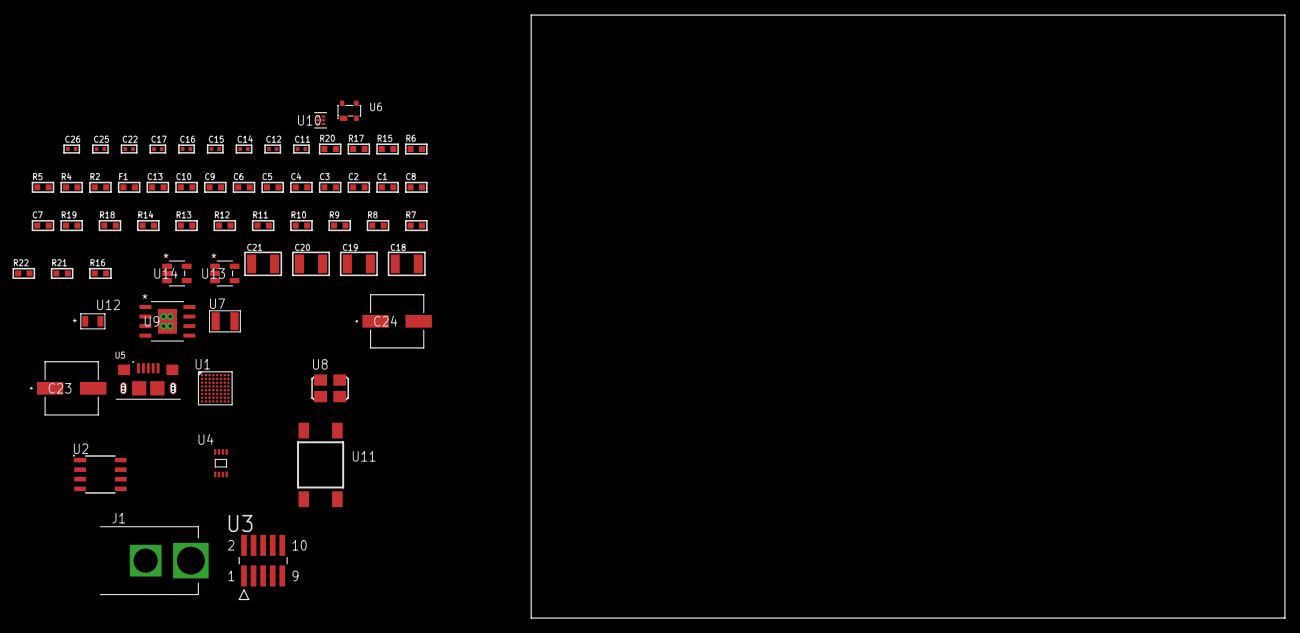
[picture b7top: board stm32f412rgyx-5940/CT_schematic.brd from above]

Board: 2 copper layers, 62 parts (0 on the bottom side), 33 nets, no tracks yet.

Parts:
C1, C10, C13: 1e-06; C0603
C2, C3, C4, C5, C6: 1e-07; C0603
C7: 4.7e-06; C0603
C8: 2.2e-06; C0603
C9: 1e-08; C0603
C11, C12: 1e-11; C0402
C14, C16, C17, C25, C26: 1e-08; C0402
C15, C22: 1e-07; C0402
C18, C19, C20, C21: 1e-05; C1210
C23, C24: 0.0001; EXV-9H
F1: 240.0; L0603
J1: PJ-037B; PJ-037B_PACKAGE
R2: 1000.0; R0603
R4: 4700.0; R0603
R5, R6, R17: 2200.0; R0603
R7, R8, R9, R10, R11, R12, R13, R14, R18, R19: 10000.0; R0603
R15: 5.0; R0603
R16: 4031.5447154472; R0603
R20: 9100.0; R0603
R21: 680000.0; R0603
R22: 120000.0; R0603
U1: STM32F412RGY6; WLCSP64
U2: AT25320B-SSHL-T; SOIC-8
U3: FTSH-105-01-L-DV-K; SAMTEC_FTSH-105-01-L-DV-K
U4: 24AA04-I/MC; TDFN-8/6MM
U5: 10118193-0001LF; FCI_10118193-0001LF
U6: prtr5v0u2ax; SOT143B
U7: ABS07-32.768KHZ-7-T
U8: ASFL1-25MHZ-NCS; ASFL1
U9: MIC5234YME; SOIC-8_EP
U10: TPS3895ADRYR; SON-6
U11: 4-1437565-2; SW_4-1437565-2
U12: Q65110A2395; LGM67K-G1J2-24-Z
U13, U14: nc7sz125m5x; NC7SZ125M5X

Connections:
CLK_CRYSTAL_U1_C7: C11.1, U1.C7, U7.1
CLK_CRYSTAL_U1_C8: C12.1, U1.C8, U7.2
CLK_U1_D8: U1.D8, U8.3
GND: C1.2, C2.2, C3.2, C4.2, C5.2, C6.2, C7.2, C8.2, C9.2, C10.2, C11.2, C12.2, C13.2, C14.2, C15.2, C16.2, C17.2, C18.2, C19.2, C20.2, C21.2, C22.2, C23.2, C24.2, C25.2, C26.2, J1.2, R2.2, R7.2, R8.2, R15.2, R17.2, R20.2, R22.2, U1.A7, U1.B1, U1.D3, U1.G8, U1.H2, U2.4, U3.3, U3.5, U4.4, U4.7, U5.5, U5.6, U5.7, U5.8, U5.9, U6.1, U8.2, U9.7, U9.EPAD, U10.2, U12.C, U13.2, U13.3, U14.1, U14.3
NET_U1_A6: R6.1, U1.A6, U4.5
NET_U1_B5: R5.1, U1.B5, U4.6
NET_U1_C6: R8.1, U1.C6
NET_U1_D4: R7.1, U1.D4
NET_U1_D7: R4.1, U1.D7, U14.4
NET_U1_F7: C9.1, C10.1, F1.1, U1.F7
NET_U1_H3: C8.1, U1.H3
NET_U1_H8: U11.3, U11.4
NET_U2_3: R9.1, U2.3
NET_U2_7: R11.1, U2.7
NET_U3_9: R15.1, U3.9
NET_U9_4: R16.2, R17.1, U9.4
NET_U10_1: R19.1, R20.1, U10.1
NET_U10_3: R21.2, R22.1, U10.3
NET_U10_4: R18.1, U10.4, U13.4, U14.2
NET_U11_1: R2.1, U11.1, U11.2
PROC_SPI1_MISO: U1.B4, U2.2
PROC_SPI1_MOSI: U1.C4, U2.5
PROC_SPI1_NSS: R10.1, U1.A2, U2.1
PROC_SPI1_SCK: U1.F5, U2.6
PROC_SYS_JTCK_SWCLK: R13.1, U1.B2, U3.4
PROC_SYS_JTDO_SWO: U1.A5, U3.6
PROC_SYS_JTMS_SWDIO: R14.1, U1.C2, U3.2
PROC_USB_OTG_FS_DM: U1.D3, U5.2, U6.3
PROC_USB_OTG_FS_DP: U1.C1, U5.3, U6.2
PROC_USB_OTG_FS_VBUS: C13.1, U1.D1, U5.1, U6.4
RST_OUT_U3_JTAG_RST_B: R12.1, U3.10, U13.1
VCC_S1_10V4: C18.1, C19.1, C23.1, C24.1, J1.1, U9.5, U9.8
VCC_TIER1_3V3: C1.1, C2.1, C3.1, C4.1, C5.1, C6.1, C7.1, C14.1, C15.1, C16.1, C17.1, C20.1, C21.1, C22.1, C25.1, C26.1, F1.2, R4.2, R5.2, R6.2, R9.2, R10.2, R11.2, R12.2, R13.2, R14.2, R16.1, R18.2, R19.2, R21.1, U1.A1, U1.A8, U1.B7, U1.H1, U1.H7, U2.8, U3.1, U4.8, U8.4, U9.1, U10.6, U13.5, U14.5
